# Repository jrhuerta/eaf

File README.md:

# MyFocuserPro2 EAF - EAF Bracket Compatible Telescope Focuser

A DIY electronic telescope focuser engineered for **heavy imaging trains** and designed to be physically compatible with standard EAF mounting brackets. Simply order the PCB from JLCPCB or PCBWay, solder a few components, 3D print the enclosure, and you'll have a robust focuser capable of handling substantial camera and filter wheel setups at a fraction of commercial prices.

## 🎯 Project Overview

This focuser is based on the MyFocuserPro2 project with modifications for standard EAF bracket compatibility. It uses a precision geared stepper motor, Arduino Nano microcontroller, and DRV8825 stepper driver, all integrated into a single compact enclosure that mounts directly to standard EAF brackets using the same bolt pattern.

**Perfect for astrophotographers** running heavy imaging setups with large cameras, filter wheels, and guide cameras - this focuser provides the torque and precision needed for reliable focusing under load.

### Key Features

- **Heavy Load Capable**: Engineered to handle substantial imaging trains with confidence
- **EAF Bracket Compatible**: Same mounting pattern and bolt spacing as standard EAF brackets
- **Simple DIY Build**: Order PCB → Solder components → Print enclosure → Done!
- **High Precision**: Uses 17hs13-0404S-PG27 geared stepper motor from StepperOnline
- **Arduino-Based**: Easy to program and modify with Arduino Nano
- **Cost-Effective**: ~$50-80 total cost vs $300+ for commercial alternatives
- **Production Ready**: Designed for easy ordering from JLCPCB/PCBWay

## 🛠️ Hardware Components

### Main Components

| Component | Part Number/Description | Quantity | Notes |
|-----------|------------------------|----------|-------|
| **Stepper Motor** | 17hs13-0404S-PG27 | 1 | Geared stepper from StepperOnline |
| **Microcontroller** | Arduino Nano | 1 | Standard Arduino Nano board |
| **Motor Driver** | DRV8825 | 1 | Pololu-compatible stepper driver |
| **Capacitor** | 100µF Electrolytic | 1 | Power supply filtering |
| **Power Connector** | DC Barrel Jack | 1 | 12V power input |
| **Motor Connector** | 4-pin Header | 1 | Stepper motor connection |

### PCB Specifications

- **Design Tool**: KiCad 9.x
- **Board Size**: Compact form factor optimized for enclosure
- **Layers**: 2-layer PCB design
- **Manufacturing**: Optimized for JLCPCB and PCBWay production
- **Power**: 12V input
- **Assembly**: Only 6 components to solder by hand

## 📁 Repository Structure

```
├── README.md                           # This file
├── enclosure/                          # 3D Printable Parts
│   ├── eaf-body.stl                   # Main enclosure body
│   └── eaf-cover.stl                  # Enclosure cover/lid
├── myfocuserpro2-eaf/                  # KiCad Project Files
│   ├── myfocuserpro2-eaf.kicad_pro    # KiCad project file
│   ├── myfocuserpro2-eaf.kicad_sch    # Schematic design
│   ├── myfocuserpro2-eaf.kicad_pcb    # PCB layout
│   ├── models/                        # 3D Models for PCB
│   │   ├── Arduino Nano.STEP          # Arduino Nano 3D model
│   │   └── DRV8825 STEPPER MOTOR...   # DRV8825 3D model
│   └── production/                    # Manufacturing Files
│       ├── bom.csv                    # Bill of Materials
│       ├── positions.csv              # Component placement
│       ├── designators.csv            # Component designators
│       ├── netlist.ipc                # Netlist for assembly
│       └── myfocuserpro2-eaf.zip     # Gerber files
```

## 🔧 Assembly Instructions

### 1. Order PCB

**JLCPCB Ordering:**
1. Go to [JLCPCB.com](https://jlcpcb.com)
2. Upload the Gerber file: `myfocuserpro2-eaf/production/myfocuserpro2-eaf.zip`
3. Use default settings (2-layer, 1.6mm thickness)
4. Order quantity: 5 boards (minimum order)
5. Cost: ~$10-15 shipped

**PCBWay Ordering:**
1. Go to [PCBWay.com](https://pcbway.com)
2. Upload the same Gerber file
3. Use default settings
4. Order quantity: 5 boards (minimum order)
5. Cost: ~$15-20 shipped

### 2. Source Components

**Total component cost: ~$30-40**

Order these components (reference `production/bom.csv` for exact specifications):
- Arduino Nano (1x) - ~$8
- DRV8825 driver board (1x) - ~$5
- 100µF electrolytic capacitor (1x) - ~$1
- DC barrel jack connector (1x) - ~$2
- Pin headers 2.54mm pitch (1x set) - ~$3
- 17hs13-0404S-PG27 stepper motor - ~$25

### 3. PCB Assembly (15 minutes)

**Required tools:** Soldering iron, solder, flux (optional)

1. **Solder Arduino Nano**: Place and solder to A1 position
2. **Solder DRV8825**: Place and solder to A2 position  
3. **Solder Capacitor**: Install C1 (mind polarity - longer leg to +)
4. **Solder Connectors**: Install J1 (4-pin), J2 (barrel jack), J3 (3-pin)
5. **Clean and inspect**: Check for cold joints and bridges

*No SMD components - all through-hole for easy hand soldering!*

#### Assembly Photos

### 4. 3D Printing (2-3 hours print time)

Print the enclosure parts from the `enclosure/` directory:

- **Files**: `eaf-body.stl` and `eaf-cover.stl`
- **Material**: PETG
- **Layer Height**: 0.2mm
- **Infill**: 20-30%
- **Print Speed**: Standard settings
- **Supports**: Minimal or none required
- **Cost**: ~$3-5 in filament

### 5. Motor Selection - Built for Heavy Loads

**Recommended Motor**: 17hs13-0404S-PG27 from StepperOnline

**Why this motor handles heavy imaging trains:**
- **27:1 Planetary Gearbox**: Massive torque multiplication for heavy loads
- **High Holding Torque**: Maintains position even with substantial weight
- **Smooth Operation**: Planetary gearing reduces vibration and backlash
- **Proven Design**: Successfully used in commercial focusers
- **Direct Mount**: No coupling required - direct attachment to focuser

**Load Capacity**: Easily handles imaging trains exceeding 3kg.

Tested with the following image train with consistent results. Commercial EAF units had issues handling this image train.

* Sharpstar ED 1x Coma corrector
* Off Axis Guider
* Wanderer Astro Rotator Mini V2
* 7x2" EFW (fully loaded)
* ASI2600MC

### 6. Final Assembly (10 minutes)

1. **Install PCB**: Place assembled PCB into printed enclosure body
2. **Connect Motor**: Stepper motor to J1 (4-pin header)
3. **Connect Power**: 12V power supply to J2 (barrel jack)
5. **Secure Cover**: Attach printed cover and test functionality
6. **Mount to Telescope**: Install using standard EAF bracket

**Total Build Time**: ~30 minutes active work + print time
**Total Cost**: ~$50 vs $300+ commercial focusers

#### Finished Product

## ⚡ Power Requirements

- **Input Voltage**: 12V DC
- **Current Draw**: < 500mA 
- **Power Connector**: Standard 2.1mm barrel jack (center positive)

## 🔌 Connections

### Motor Connection (J1)
```
Pin 1: A+    (Motor Phase A)
Pin 2: A-    (Motor Phase A)
Pin 3: B+    (Motor Phase B)
Pin 4: B-    (Motor Phase B)
```

### Control Interface (J3)
```
Pin 1: GND   (Ground)
Pin 2: IN    (Input/Button)
Pin 3: VCC   (3.3V/5V)
```

## 💻 Software

This hardware is designed to work with MyFocuserPro2 firmware or compatible Arduino-based focuser software. The Arduino Nano can be programmed via USB using the Arduino IDE.

**Recommended Software**:
- MyFocuserPro2 firmware
- ASCOM drivers for Windows
- INDI drivers for Linux

## 🔗 Compatibility

### Mechanical Compatibility
- **EAF Bracket**: Direct mounting compatibility with standard EAF bracket bolt pattern
- **Telescope Interfaces**: Standard focuser mounting patterns
- **Motor Coupling**: 17hs13-0404S-PG27 optimized design

### Software Compatibility
- **ASCOM**: Via MyFocuserPro2 drivers
- **INDI**: Linux astronomy software
- **Custom Software**: Arduino-programmable for custom implementations

## 📋 Bill of Materials (BOM)

| Designator | Component | Value/Part Number | Quantity |
|------------|-----------|-------------------|----------|
| A1 | Arduino Nano | Standard Arduino Nano | 1 |
| A2 | DRV8825 | Stepper Motor Driver | 1 |
| C1 | Electrolytic Capacitor | 100µF | 1 |
| J1 | Pin Header | 4-pin, 2.54mm | 1 |
| J2 | Barrel Jack | DC Power Jack | 1 |

*Complete BOM with part numbers available in `myfocuserpro2-eaf/production/bom.csv`*

## 📐 Mechanical Specifications

- **Load Capacity**: 3-5kg+ imaging trains (6-11+ lbs)
- **Mounting**: Standard EAF bracket bolt pattern and center spacing
- **Enclosure Dimensions**: Optimized for EAF bracket compatibility
- **Weight**: Approximately 200-300g (depending on motor)
- **Motor Output**: Direct coupling to focuser mechanism
- **Backlash**: Minimal due to planetary gearbox design
- **Resolution**: Sub-micron focusing steps with geared motor

## 🚀 Getting Started - Quick Build Guide

**Total Cost: ~$50-80 | Build Time: ~30 minutes + 3 hours printing**

1. **Order PCB**: Upload Gerber files to JLCPCB or PCBWay (~$10-15)
2. **Buy Components**: Arduino Nano, DRV8825, motor, and basic parts (~$30-40)
3. **Order Motor**: 17hs13-0404S-PG27 from StepperOnline (~$25)
4. **3D Print**: Print enclosure parts (~$3-5 filament cost)
5. **Assemble**: 15 minutes soldering + 10 minutes final assembly
6. **Install Software**: Load MyFocuserPro2 firmware
7. **Mount and Focus**: Attach to telescope and enjoy precision focusing!

**Perfect for:**
- Heavy imaging setups (large cameras + filter wheels)
- Long focal length telescopes requiring precise focusing
- Astrophotographers wanting reliable, affordable automation
- Anyone tired of manual focusing with heavy equipment

## 🤝 Contributing

This is an open-source project. Contributions are welcome for:
- PCB improvements and optimizations
- Enclosure design enhancements
- Software compatibility updates
- Documentation improvements

## 📄 License

This project is open source. Please check individual file headers and project documentation for specific licensing terms.

## 🛠️ Support

For technical support and questions:
- Check existing issues and documentation
- Review MyFocuserPro2 project documentation
- Consult KiCad files for detailed design information

## 🔗 Related Projects

- **MyFocuserPro2**: Base project this design is derived from
- **StepperOnline**: Source for recommended geared stepper motor

---

**Note**: This project requires basic electronics assembly skills and access to PCB manufacturing services. Ensure you have appropriate tools and experience before beginning assembly.

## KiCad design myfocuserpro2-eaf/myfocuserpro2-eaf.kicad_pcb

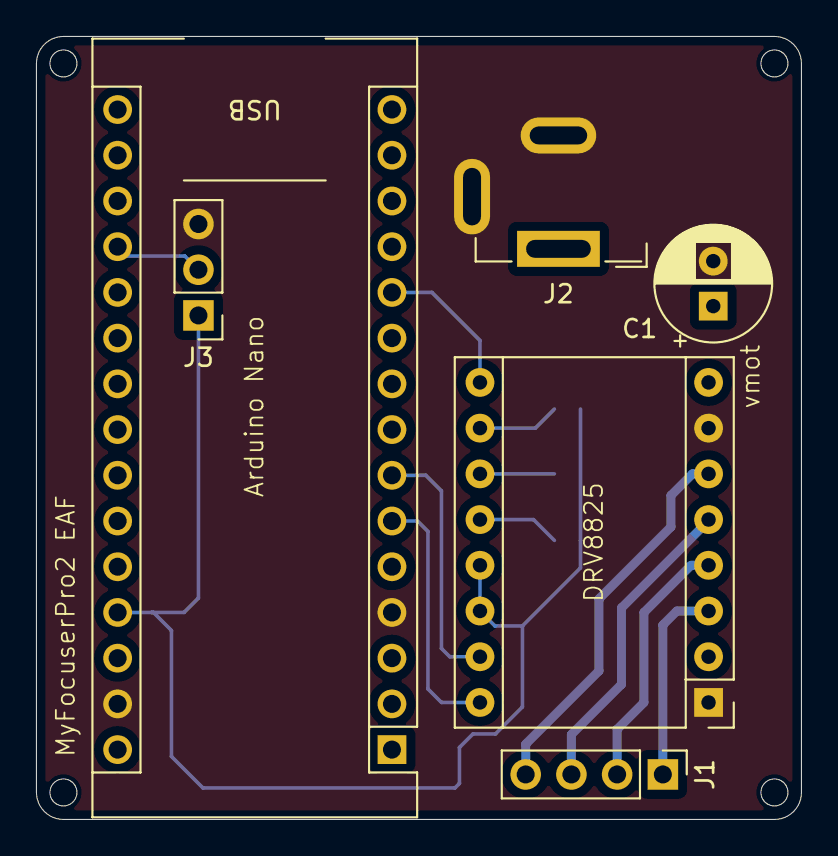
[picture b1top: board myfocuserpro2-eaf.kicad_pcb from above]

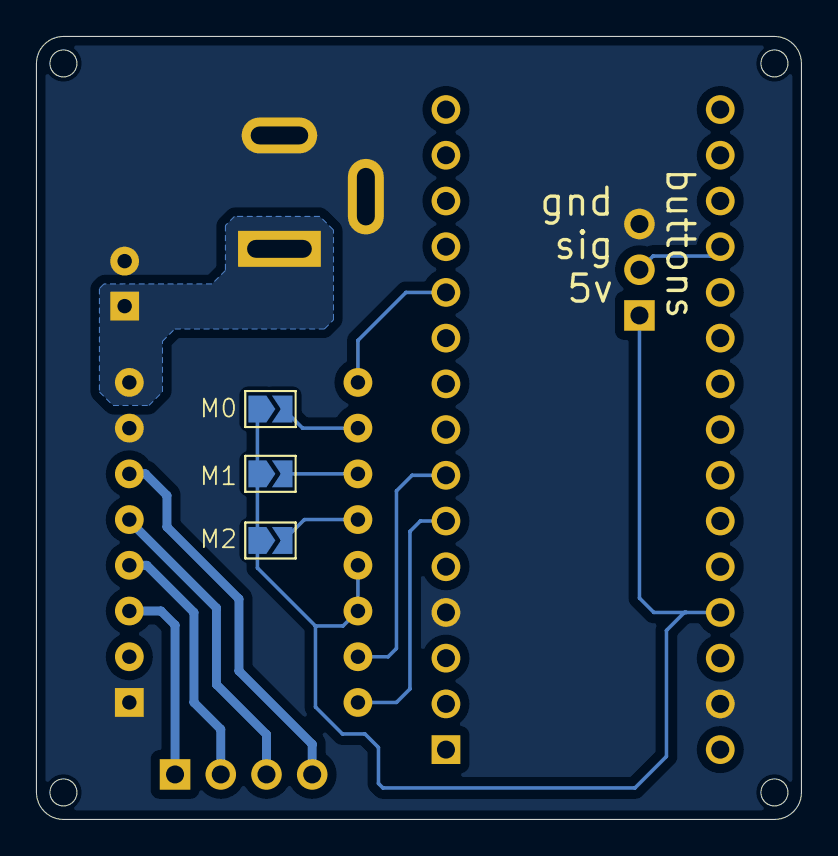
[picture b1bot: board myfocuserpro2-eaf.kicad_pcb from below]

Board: 2 copper layers, 42.5 x 43.5 mm, 13 parts (3 on the bottom side), 14 nets.

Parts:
A1: Arduino_Nano
A2: DRV8825; Pololu_Breakout-16_15.2x20.3mm
C1: 100uF; CP_Radial_D6.3mm_P2.50mm
H1, H2, H3, H4: MountingHole; MountingHole_1.5mm
J1: Conn_01x04; PinHeader_1x04_P2.54mm_Vertical
J2: 12V; BarrelJack_GCT_DCJ200-10-A_Horizontal
J3: buttons; PinHeader_1x03_P2.54mm_Vertical
JP1, JP2, JP3: SolderJumper_2_Open; SolderJumper-2_P1.3mm_Open_TrianglePad1.0x1.5mm

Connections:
+5V: A1.27 (+5V), A2.13 (~RST), A2.14 (~SLP), J3.1, JP1.1 (A), JP2.1 (A), JP3.1 (A)
/BUTTON: A1.19 (A0), J3.2
GND: A1.4 (GND), A1.29 (GND), A2.1 (GND), A2.7 (GND), C1.2, J2.2, J2.3, J3.3
unnamed: A1.6 (D3), A2.16 (DIR)
unnamed: A1.7 (D4), A2.15 (STEP)
unnamed: A1.11 (D8), A2.9 (~EN)
unnamed: A2.4 (A1), J1.2
unnamed: A2.3 (A2), J1.1
unnamed: A2.5 (B1), J1.3
unnamed: A2.6 (B2), J1.4
unnamed: A2.10 (M0), JP1.2 (B)
unnamed: A2.11 (M1), JP2.2 (B)
unnamed: A2.12 (M2), JP3.2 (B)
unnamed: A2.8 (VMOT), C1.1, J2.1

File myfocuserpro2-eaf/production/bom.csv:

Designator,Footprint,Quantity,Value,LCSC Part #
A1,Arduino_Nano,1,Arduino_Nano,
A2,Pololu_Breakout-16_15.2x20.3mm,1,DRV8825,
C1,CP_Radial_D6.3mm_P2.50mm,1,100uF,
J1,PinHeader_1x04_P2.54mm_Vertical,1,Conn_01x04,
J2,BarrelJack_GCT_DCJ200-10-A_Horizontal,1,12V,
J3,PinHeader_1x03_P2.54mm_Vertical,1,buttons,

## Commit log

2025-10-19 Add initial content to README.md
2025-10-19 Initial commit.
2025-10-19 Adding some images.
2025-10-20 Adding assembly and finished images.

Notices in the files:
README.md:
License: Open Source
